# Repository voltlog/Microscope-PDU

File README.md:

# Microscope-PDU
My trinocular microscope has served me well for a few years but it has one annoying thing, the fact that it uses 3 different power adapters: one to supply power to the camera, one for the monitor and another one for the LED lights. This obviously takes up 3 different sockets on my extension lead and creates a mess of wires.

My solution to the problem is this Power Distribution Unit where I have a single 12V input and 3 outputs to feed the required voltages. The board was designed to be configurable, so you have the option of installing a standard footprint dc-dc converter if you need different voltages.

## Links for the additional items you will need
→Enclosure used in the project
https://voltlog.com/y/rpw6u<br />
→DC barrel jack extension leads
Aliexpress https://voltlog.com/y/x1zli

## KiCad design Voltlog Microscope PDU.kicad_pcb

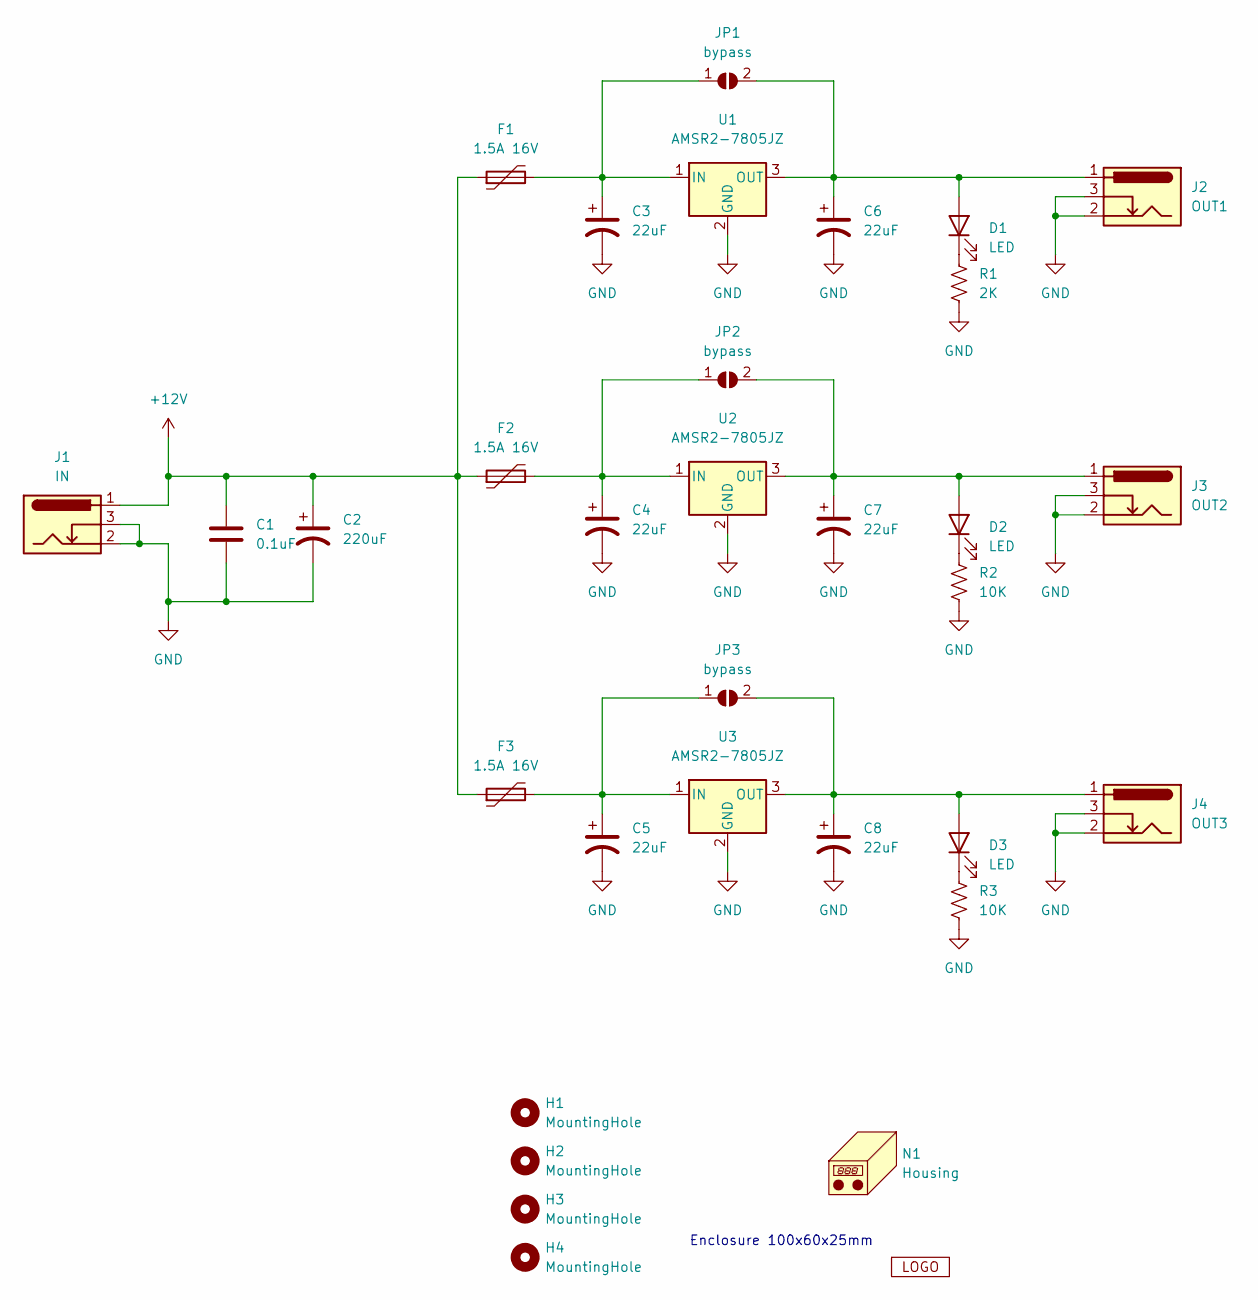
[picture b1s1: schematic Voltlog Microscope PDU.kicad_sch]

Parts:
C1: 0.1uF; C_0603_1608Metric
C2: 220uF; CP_Elec_8x10
C3, C4, C5, C6, C7, C8: 22uF; CP_Elec_6.3x5.4
D1, D2, D3: LED; LED_0603_1608Metric
F1, F2, F3: 1.5A 16V; Fuse_1812_4532Metric
H1, H2, H3, H4: MountingHole; MountingHole_3.2mm_M3
J1: IN; BarrelJack_CLIFF_FC681465S_SMT_Horizontal; LCSC C2987414
J2: OUT1; BarrelJack_CLIFF_FC681465S_SMT_Horizontal; LCSC C2987414
J3: OUT2; BarrelJack_CLIFF_FC681465S_SMT_Horizontal; LCSC C2987414
J4: OUT3; BarrelJack_CLIFF_FC681465S_SMT_Horizontal; LCSC C2987414
JP1, JP2, JP3: bypass; SolderJumper-2_P1.3mm_Open_RoundedPad1.0x1.5mm
N1: Housing
R1: 2K; R_0603_1608Metric
R2, R3: 10K; R_0603_1608Metric
U1, U2, U3: AMSR2-7805JZ; Converter_DCDC_RECOM_R-78HB-0.5L_THT
V1: VOLTLOG_LOGO; voltlog_mask_5mm

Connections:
+12V: C1.1, C2.1, F1.1, F2.1, F3.1, J1.1
GND: C1.2, C2.2, C3.2, C4.2, C5.2, C6.2, C7.2, C8.2, J1.2, J1.3, J2.2, J2.3, J3.2, J3.3, J4.2, J4.3, R1.1, R2.1, R3.1, U1.2 (GND), U2.2 (GND), U3.2 (GND)
unnamed: C3.1, F1.2, JP1.1 (A), U1.1 (IN)
unnamed: C4.1, F2.2, JP2.1 (A), U2.1 (IN)
unnamed: C5.1, F3.2, JP3.1 (A), U3.1 (IN)
unnamed: C6.1, D1.2 (A), J2.1, JP1.2 (B), U1.3 (OUT)
unnamed: C7.1, D2.2 (A), J3.1, JP2.2 (B), U2.3 (OUT)
unnamed: C8.1, D3.2 (A), J4.1, JP3.2 (B), U3.3 (OUT)
unnamed: D1.1 (K), R1.2
unnamed: D2.1 (K), R2.2
unnamed: D3.1 (K), R3.2

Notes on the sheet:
Enclosure 100x60x25mm

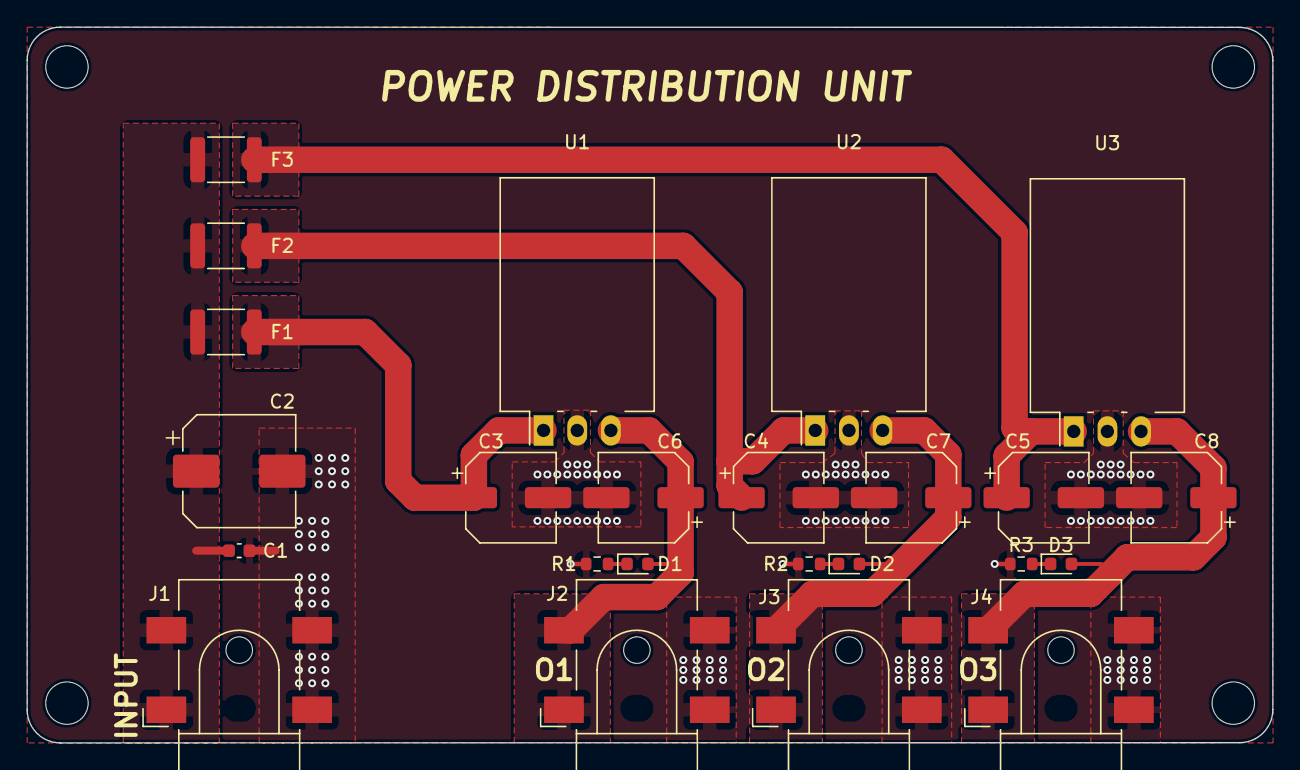
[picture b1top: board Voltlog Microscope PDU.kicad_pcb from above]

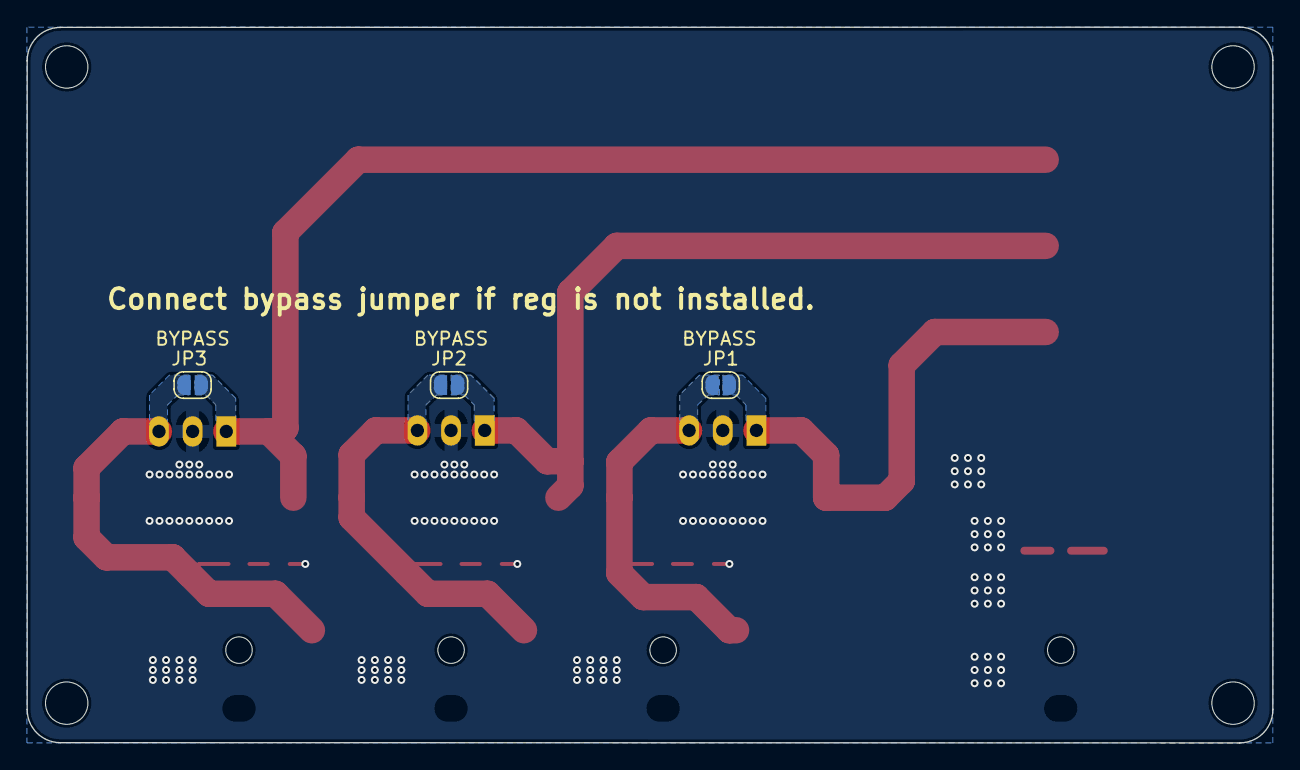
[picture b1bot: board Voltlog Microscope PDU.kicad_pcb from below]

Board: 2 copper layers, 94.0 x 54.0 mm, 32 parts (3 on the bottom side), 11 nets.
